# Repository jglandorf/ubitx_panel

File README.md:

### Wiring Harness PCB Panel for the µBITX  
The [µBITX](http://www.hfsignals.com/index.php/ubitx/) is "The QRP HF General Coverage Transceiver you can build".  
 * Speeds wiring to the µBITX mic, speaker, and keyer sockets, and encoder  
 * Encoder on breakaway PCB section allows for separate mounting location  
 * Reduces wiring errors  
 * Allows use of an inexpensive Baofeng speaker mic  
 * Easily mounts to an enclosure  
 * Schematic, PCB in [Kicad 5](http://www.kicad-pcb.org/download/)  

See [docs/ubitx_panel_usage.pdf](docs/ubitx_panel_usage.pdf) for a complete description.  
Used successfully for the [Arrow Communications Assn.](https://w8rp.org/) uBitx build sessions.  

73
Joe, AC8ES

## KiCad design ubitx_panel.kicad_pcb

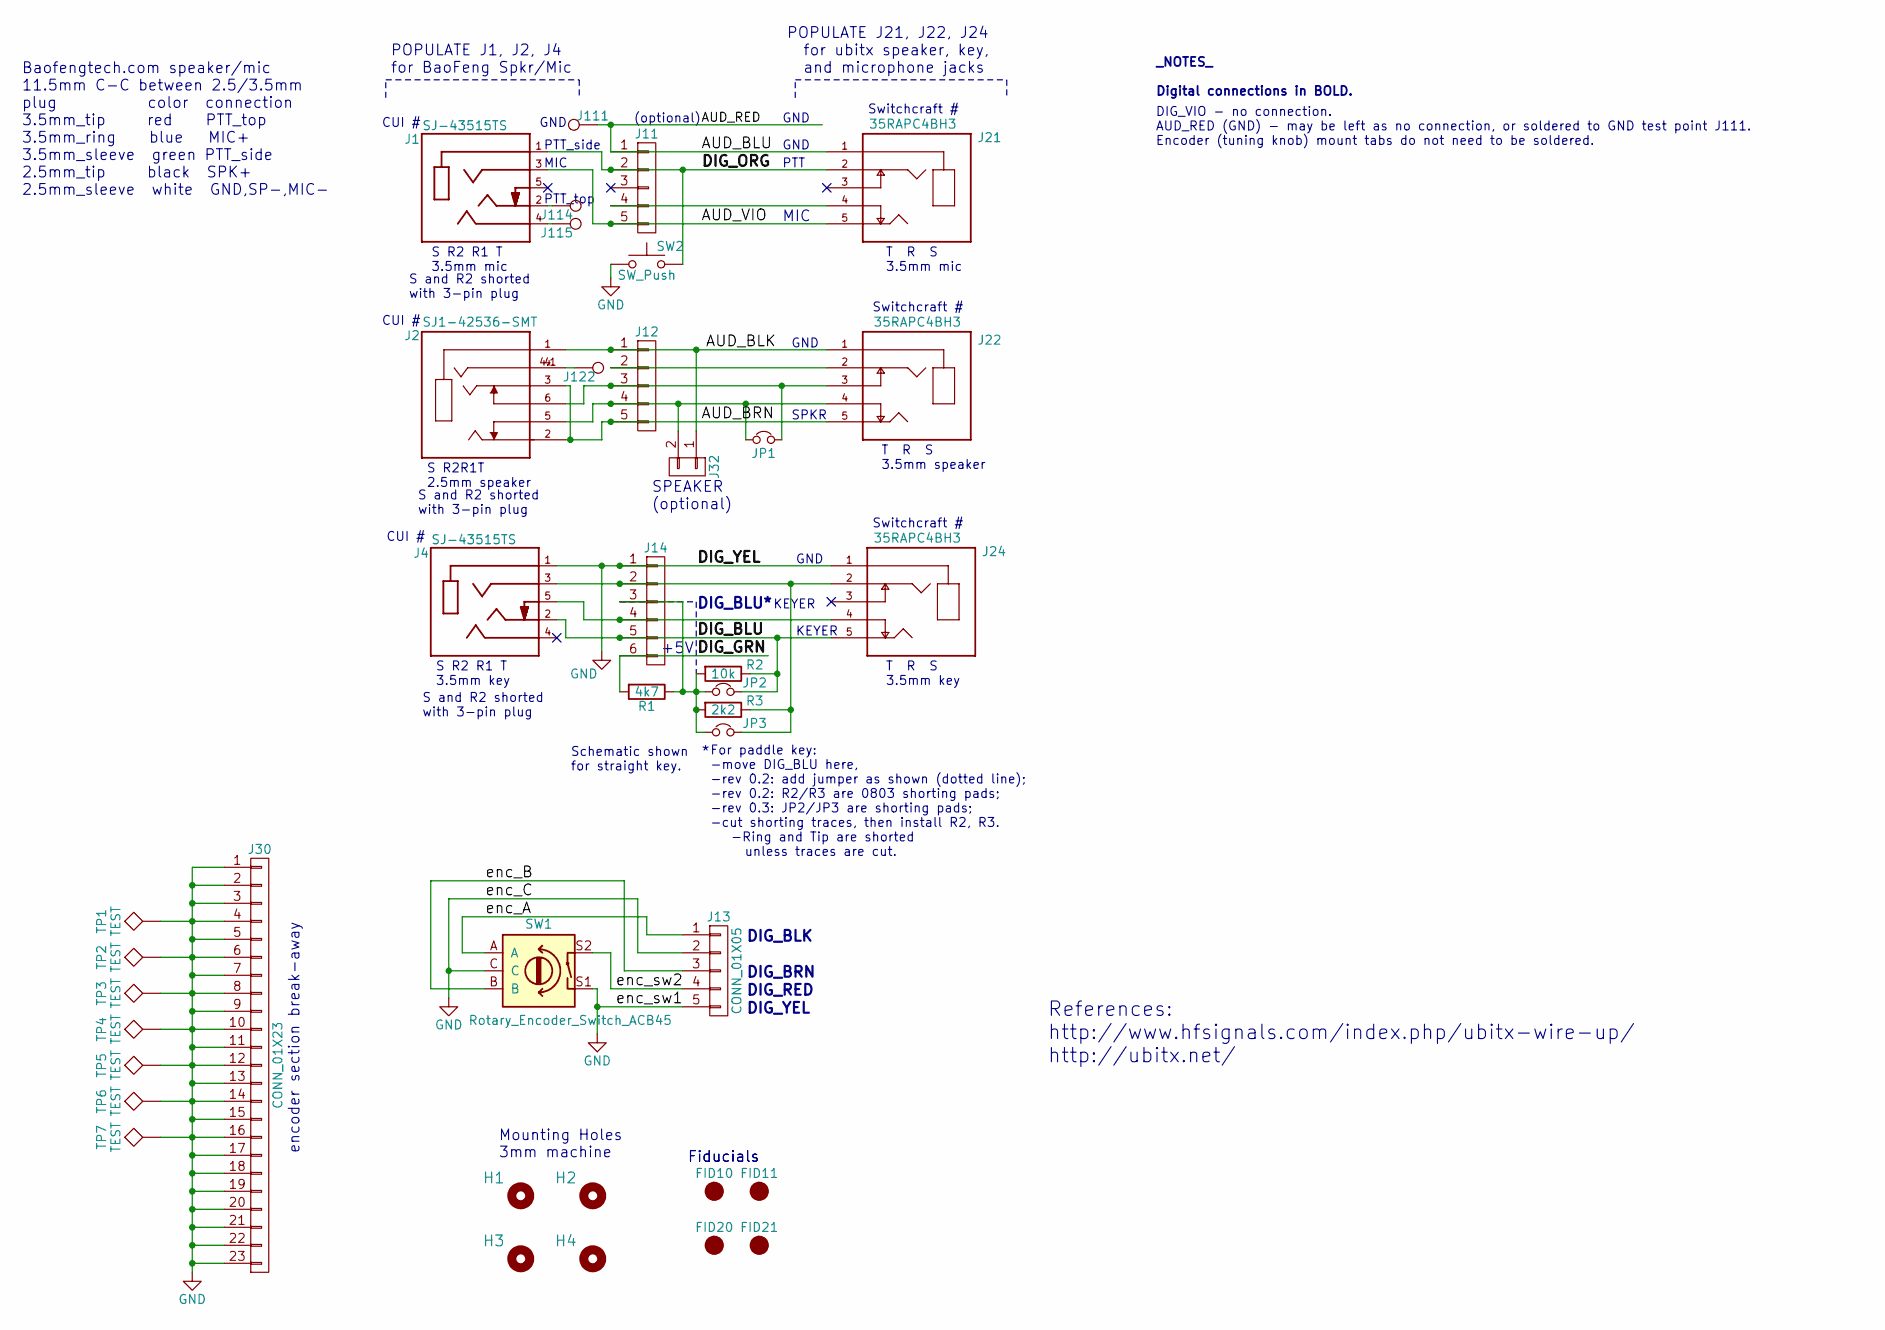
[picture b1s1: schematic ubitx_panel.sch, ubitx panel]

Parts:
FID10, FID11: CIRCLE1mmDia; Fiducial_1mm_Dia_2.54mm_Outer_CopperTop; MPN DNP
FID20, FID21: CIRCLE1mmDia; Fiducial_1mm_Dia_2.54mm_Outer_CopperBottom; MPN DNP
H1, H2: 3mm_Mounting_Hole; NPTH_3mm_ID; MPN DNP
H3, H4: 3mm_Mounting_Hole_Unlocked; NPTH_3mm_ID_Unlocked; MPN DNP
J1, J4: SJ-43515TS; CUI_SJ-43515TS
J2: SJ1-42536-SMT; CUI_SJ1-42536-SMT-move4
J11, J12, J13: CONN_01X05; Pin_Header_Straight_1x05_Pitch2.54mm
J14: CONN_01X06; Pin_Header_Straight_1x06_Pitch2.54mm
J21, J22, J24: 35RAPC4BH3; SWITCHCRAFT_35RAPC4BH3
J30: CONN_01X23; Pin_Header_Straight_1x23_Pitch1.27mm
J32: CONN_01X02; Pin_Header_Straight_1x02_Pitch2.54mm
J111: TEST_1P; SolderWirePad_single_0-8mmDrill
J114, J115, J122: TEST_1P; Socket_Strip_Straight_1x01_Pitch2.54mm
JP1, JP2, JP3: Jumper_NC_Small; SolderJumper-2_P1.3mm_Bridged_RoundedPad1.0x1.5mm
R1: 4k7; R_Axial_DIN0204_L3.6mm_D1.6mm_P2.54mm_Vertical
R2: 10k; R_Axial_DIN0204_L3.6mm_D1.6mm_P2.54mm_Vertical
R3: 2k2; R_Axial_DIN0204_L3.6mm_D1.6mm_P2.54mm_Vertical
SW1: Rotary_Encoder_Switch_ACB45; RotaryEncoder_Alps_EC11E-Switch_Vertical_H20mm_CircularMoun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; MPN PEC11R-4015F-S0024
SW2: SW_Push; SW_Tactile_SPST_Angled
TP1, TP2, TP3, TP4, TP5, TP6, TP7: TEST; SolderWirePad_single_0-8mmDrill

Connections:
/AUD_BLK: J2.1, J12.1, J22.1, J32.1
/AUD_BLU: J11.1, J21.1, J111.1
/AUD_BRN: J2.2, J2.3, J12.5, J22.5
/AUD_VIO: J1.3 (RING1), J11.5, J21.5
/DIG_BLU: J4.2 (TIP), J14.5, J24.5, JP2.2, R2.1
/DIG_GRN: J14.6, R1.2
/DIG_ORG: J1.1 (SLEEVE), J11.2, J21.2, SW2.2
/enc_A: J13.1, SW1.A
/enc_B: J13.3, SW1.B
/enc_sw2: J13.4, SW1.S2
GND: J4.1 (SLEEVE), J13.2, J13.5, J14.1, J24.1, J30.1, J30.2, J30.3, J30.4, J30.5, J30.6, J30.7, J30.8, J30.9, J30.10, J30.11, J30.12, J30.13, J30.14, J30.15, J30.16, J30.17, J30.18, J30.19, J30.20, J30.21, J30.22, J30.23, SW1.C, SW1.S1, SW2.1, TP1.1, TP2.1, TP3.1, TP4.1, TP5.1, TP6.1, TP7.1
unnamed: J1.2 (TIP), J114.1
unnamed: J1.4 (RING2), J115.1
unnamed: J11.4, J21.4
unnamed: J12.2, J22.2
unnamed: J2.6, J12.3, J22.3, JP1.2
unnamed: J2.5, J12.4, J22.4, J32.2, JP1.1
unnamed: J4.3 (RING1), J14.2, J24.2, JP3.2, R3.1
unnamed: J14.3, JP2.1, JP3.1, R1.1, R2.2, R3.2
unnamed: J4.5 (TIP_SWITCH), J14.4, J24.4
unnamed: J2.4, J2.4.1 (4), J122.1

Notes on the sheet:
Mounting Holes 3mm machine
Fiducials
S R2 R1 T 3.5mm mic
T R S 3.5mm mic
T R S 3.5mm speaker
S R2R1T 2.5mm speaker
S R2 R1 T 3.5mm key
T R S 3.5mm key
DIG_RED
DIG_YEL
DIG_BLK
DIG_BRN
Baofengtech.com speaker/mic 11.5mm C-C between 2.5/3.5mm plug color connection 3.5mm_tip red PTT_top 3.5mm_ring blue MIC+ 3.5mm_sleeve green PTT_side 2.5mm_tip black SPK+ 2.5mm_sleeve white GND,SP-,MIC-
S and R2 shorted with 3-pin plug
MIC
PTT
GND
SPKR
PTT_side
PTT_top
encoder section break-away
POPULATE J1, J2, J4 for BaoFeng Spkr/Mic
POPULATE J21, J22, J24 for ubitx speaker, key, and microphone jacks
References: http://www.hfsignals.com/index.php/ubitx-wire-up/ http://ubitx.net/
SPEAKER (optional)
KEYER
_NOTES_ Digital connections in BOLD.
(optional)
DIG_VIO - no connection. AUD_RED (GND) - may be left as no connection, or soldered to GND test point J111. Encoder (tuning knob) mount tabs do not need to be soldered.
CUI #
+5V
Switchcraft #
DIG_BLU*
Schematic shown for straight key.
For paddle key: -move DIG_BLU here, -rev 0.2: add jumper as shown (dotted line); -rev 0.2: R2/R3 are 0803 shorting pads; -rev 0.3: JP2/JP3 are shorting pads; -cut shorting traces, then install R2, R3. -Ring and Tip are shorted unless traces are cut.

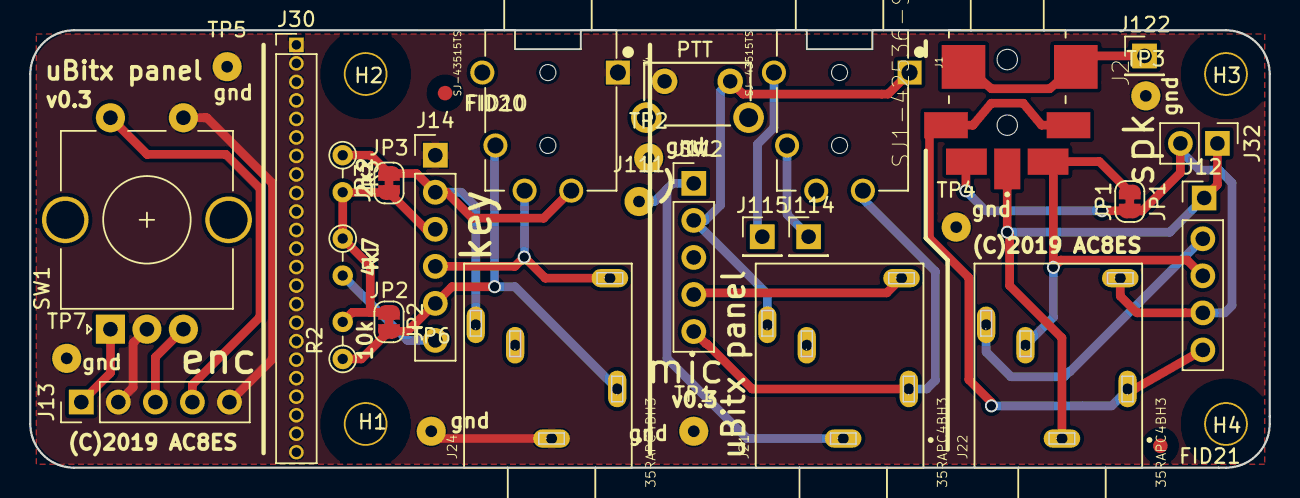
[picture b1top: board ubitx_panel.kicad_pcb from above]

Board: 2 copper layers, 85.0 x 30.0 mm, 39 parts (0 on the bottom side), 21 nets.

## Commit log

2019-10-02 Wiring Harness PCB Panel for the µBITX
    A Wiring Harness PCB Panel for the µBITX.
2019-10-02 edit readme, add photo
    edit readme, add photo
2019-10-17 Added dimensions for mounting
    Added dimensions for mounting holes, board outline, and connector centerline spacing.

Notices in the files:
ubitx_panel.kicad_pcb:
(C)2019 AC8ES
